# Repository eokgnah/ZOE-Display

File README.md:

# ZOE CAN ESP32

Bei diesem Projekt handelt es sich um eine Display-Platine zum Auslesen von Fahrzeugdaten (z.B. State of Health, Ladeleistung, Reifendruck) für die Renault ZOE Phase 1 (Q210, R210, R240, Q90, R90, R110, nur bis 2019).

Das Display wird mittels einer 3D-druckbaren Halterung in die Ablage unterhalb des R-Link eingelegt und über den direkt darunterliegenden OBD-Port an den CAN-Bus des Fahrzeugs angeschlossen. Es verwendet einen ESP32-Mikrocontroller mit WLAN-Funktionalität und kann per Webbrowser konfiguriert werden. 

Weitere Informationen und Bilder gibt es im GoingElectric-Forum unter https://www.goingelectric.de/forum/viewtopic.php?t=37914

Platine V5 wird über den USB-Port des R-Link mit Strom versorgt. 

Bei den Platinen V7 und V8 erfolgt die Stromversorgung über den OBD-Port. Hierbei schaltet sich die Platine beim Aufschließen des Fahrzeugs oder Starten eines Ladevorgangs automatisch ein (sobald der CAN-Bus aktiv ist). Nach Abschließen des Fahrzeugs bzw. Beendigung des Ladevorgangs kann sich das Display nach einer konfigurierbaren Zeitdauer auch selbst wieder ausschalten.
Optional kann eine USB-Buchse integriert werden, über welche beispielsweise Mobilgeräte aufgeladen werden können.

Für die Platine V8 existiert eine ausführliche Lötanleitung unter https://github.com/eokgnah/ZOE-Display/blob/master/Platine%20V8/README.md.
Der Aufbau sollte damit auch für Unerfahrene kein allzu großes Problem darstellen.

<pre>
!!!!!!!!!!!!!!!!!!!!!!!!!!!!!!!!!!!!!!!!!!!!!!!!!!!!!!!!!!!!!!!!!!
!!!! OHNE GEWÄHR, ALLES AUF EIGENE GEFAHR, NUR ZU TESTZWECKEN !!!!
!!!!!!!!!!!!!!!!!!!!!!!!!!!!!!!!!!!!!!!!!!!!!!!!!!!!!!!!!!!!!!!!!!
</pre>

## Verwendete Bauteile

- ESP32-Development-Board 38-Pin-Variante (z.B. https://www.berrybase.de/esp32-nodemcu-development-board oder https://www.ebay.de/itm/122795614934 oder https://www.amazon.de/gp/product/B071P98VTG)
- 2,8 Zoll 240 x 320 SPI TFT Panel resistiver Touchscreen (mit Display-Treiber ILI9341, z.B. https://www.ebay.de/itm/284811606229 oder https://www.amazon.de/dp/product/B082QVKT7M oder https://de.aliexpress.com/item/1005002233178546.html [Variante TL9341])
- alternativ mit kapazitivem Touchscreen (Adafruit 1947 mit Display-Treiber ILI9341, z.B. https://www.exp-tech.de/displays/tft/5430/adafruit-2.8-tft-touch-shield-for-arduino-w/capacitive-touch oder https://www.amazon.de/gp/product/B00R3R65C0/ oder https://www.mouser.de/ProductDetail/Adafruit/1947?qs=GURawfaeGuArmJSJoJoDJA%3D%3D)
- SD-Karte (bei resistivem Touchscreen) bzw. microSD-Karte (bei kapazitivem Touchscreen)
- optional GPS-Modul NEO-6M (z.B. https://www.berrybase.de/u-blox-neo-6m-gps-ttl-empfaenger-inkl.-antenne oder https://www.amazon.de/gp/product/B088LR3488 oder https://www.ebay.de/itm/265640015319)
- Kleinteile (siehe Ordner zur jeweiligen Platinen-Version)

## Verbindungen mit resistivem Touchscreen
<pre>
ESP32 Dev Board Pinout

Wohin           Bezeich.       ESP32 Pins       Bezeich.    Wohin

                            3V3         GND
                            EN          G23     MOSI        Display,Touch,SD
                ST          G36         G22
                            G39         G1      (TX)
                            G34         G3      (RX)
                (CAN2 RX)   G35         G21     CS          Touch
                (CAN2 TX)   G32         GND
                HR          G33         G19     MISO        Display,Touch,SD
                            G25         G18     SCLK        Display,Touch,SD
GPS-Modul       GPS TX      G26         G5 
GPS-Modul       GPS RX      G27         G17     CAN TX      OBD-Anschluss
BUZZER+                     G14         G16     CAN RX      OBD-Anschluss
                POWER OFF   G12         G4      RST         Display
                            GND         G0      (BOOT)
SD              CS          G13         G2      DC          Display
                (Flash)     G9          G15     CS          Display
                (Flash)     G10         G8      (Flash)
                (Flash)     G11         G7      (Flash)
                            5V          G6      (Flash)
</pre>                    
RX und TX gibt den Pin an, mit dem es verbunden werden muss. GPS TX muss also auf den Pin
TX am GPS Modul! 

CAN2 ist derzeit experimentell. 

ST = Screen Turn, ST=1 (verbinden mit 3V3) -> Bildschirm um 180 Grad gedreht

HR = Helligkeitsregelung, kann einen Transistor ansteuern, über den die LED-Hintergrundbeleuchtung des Displays gedimmt werden kann.

POWER OFF = Ausschalt-Pin für die Stromversorgung über den OBD-Port

## Verbindungen mit kapazitivem Touchscreen
<pre>
ESP32 Dev Board Pinout

Wohin           Bezeich.       ESP32 Pins       Bezeich.    Wohin

                            3V3         GND
                            EN          G23     SPI MOSI    Display
                ST          G36         G22     I²C SCL     Display
                            G39         G1      (TX)
                            G34         G3      (RX)
                (CAN2 RX)   G35         G21 
                (CAN2 TX)   G32         GND
Display         HR          G33         G19     SPI MISO    Display
Display         I²C SDA     G25         G18     SPI SCLK    Display
GPS-Modul       GPS TX      G26         G5
GPS-Modul       GPS RX      G27         G17     CAN TX      OBD-Anschluss
BUZZER+                     G14         G16     CAN RX      OBD-Anschluss
                POWER OFF   G12         G4      RST         Display
                            GND         G0      (BOOT)
Display         CARDCS      G13         G2      DC          Display
                (Flash)     G9          G15     CS          Display
                (Flash)     G10         G8      (Flash)
                (Flash)     G11         G7      (Flash)
                            5V          G6      (Flash)
</pre>                    
RX und TX gibt den Pin an, mit dem es verbunden werden muss. GPS TX muss also auf den Pin
TX am GPS Modul! 

CAN2 ist derzeit experimentell. 

ST = Screen Turn, ST=1 (verbinden mit 3V3) -> Bildschirm um 180 Grad gedreht

HR = Helligkeitsregelung, an Pin GPIO33 liegt ein PWM Signal an, welches über Pin D5 am Display
(neben CARDCS) die Regelung der Displayhelligkeit erlaubt. Achtung: Die Lötbrücke #5 auf der 
Displayplatine muss hierfür gesetzt werden.

POWER OFF = Ausschalt-Pin für die Stromversorgung über den OBD-Port
                    
## Allgemein
-  Beim Betrieb des resistiven Displays mit 3,3 V sollte der Jumper J1 am Display gesetzt (verbunden) werden (Ausschalten
des Spannungsreglers des Displays, sonst sinken die 3,3 V auf irgendwas unter 3 V). Der Touch IRQ Pin bleibt leer.
- Das Display mit kapazitivem Touchscreen erhält 5 V Versorgungsspannung. Falls das verwendete Display keine IOREF-Lötbrücke besitzt bzw. diese auf 5 V gesetzt wurde, muss eine geeignete Maßnahme vorgesehen werden, um die Spannungspegel am I²C-Bus auf max. 3,3 V zu begrenzen (das Display zieht die Leitungen nämlich mit 10-kΩ-Pull-Up-Widerständen gegen 5 V).

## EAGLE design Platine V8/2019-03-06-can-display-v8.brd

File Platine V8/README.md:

# Platine V8 — Lötanleitung

von Michi (Kontakt: kepppfeff@outlook.de oder im GoingElectric-Forum: kepppfeff-ZOE)

<pre>
!!!!!!!!!!!!!!!!!!!!!!!!!!!!!!!!!!!!!!!!!!!!!!!!!!!!!!!!!!!!!!!!!!
!!!! OHNE GEWÄHR, ALLES AUF EIGENE GEFAHR, NUR ZU TESTZWECKEN !!!!
!!!!!!!!!!!!!!!!!!!!!!!!!!!!!!!!!!!!!!!!!!!!!!!!!!!!!!!!!!!!!!!!!!
</pre>

## Benötigte Bauteile

Zusätzlich zu den unter https://github.com/eokgnah/ZOE-Display/blob/master/README.md aufgelisteten Hauptkomponenten und dem 3D-Druck werden die folgenden Bauteile benötigt. 

#### Module & Halbleiter
- U2: Spannungsregler OKI-78SR-5/1.5-W36-C oder vergleichbar (Ausgang 5 V, 1500...2000 mA)
  - Bezugsquellen: z.B. https://www.tme.eu/de/details/amsr2-7805jz/dc-dc-wandler/aimtec/ oder https://www.reichelt.de/dc-dc-wandler-oki-78sr-8-w-5-v-1500-ma-sil-single-oki515w36c-p140735.html oder https://www.voelkner.de/products/1038830/
  - Falls keine USB-Buchse an die Platine angeschlossen werden soll, kann stattdessen auch ein schwächerer (günstigerer) Spannungsregler verwendet werden, z.B. LC78_05-0.5 oder vergleichbar (Ausgang 5 V, 500 mA)
- U3: Spannungsregler LC78_03-0.5 oder LMO78_03-0.5 oder vergleichbar (Ausgang 3,3 V, 500 mA)
  - Bezugsquellen: z.B. https://www.tme.eu/de/details/amsro-783.3-nz/dc-dc-wandler/aimtec/ oder https://www.reichelt.de/dc-dc-wandler-1-65-w-3-3-v-500-ma-sil-lmo78-03-0-5-p242833.html oder https://www.voelkner.de/products/1038822/
  - Stattdessen kann auch der interne Spannungsregler des ESP32-Boards verwendet werden, dieser ist jedoch nicht so effizient und sorgt für zusätzliche Aufheizung des Mikrocontrollers, was evtl. dessen Lebensdauer verringert.
- Q1: P-Kanal-MOSFET IRFU9024N
- IC4: CAN-Transceiver MCP2562 (DIP8)
- D3, D4: Schottky-Dioden 1N5817
- T1: NPN-Transistor BC547C (nur bei Verwendung des kapazitiven Displays)
- T4: PNP-Transistor BC327-25
- T5, T6: NPN-Transistoren BC547C

#### Passive Bauelemente
- R1: Widerstand 100 kΩ ± 50 % (nur bei Verwendung des kapazitiven Displays)
- R3: Widerstand 1,5 kΩ ± 5 % (nur bei Verwendung des resistiven Displays mit eingebautem Transistor, siehe weiter unten) bzw. Widerstand 5,1 Ω ± 5 % (nur bei Verwendung des resistiven Displays ohne eingebauten Transistor, siehe weiter unten)
- R4: Widerstand 15 kΩ ± 5 % (nur bei Verwendung des kapazitiven Displays der alten Version, siehe weiter unten)
- R5: Widerstand 120 Ω ± 10 %
- R6: Widerstand 15 kΩ ± 5 %
- R7: Widerstand 15 kΩ ± 5 % (nur bei Verwendung des kapazitiven Displays der alten Version, siehe weiter unten)
- R8: Widerstand 100 kΩ ± 5 %
- R9: Widerstand 470 kΩ ± 10 %
- R10, R11: Widerstände 1,2 MΩ ± 5 %
- R12: Widerstand 470 kΩ ± 5 %
- R13: Widerstand 47 kΩ ± 5 %
- C1: Elektrolyt-Kondensator 10 μF, min. 10 V
- C2, C3, C4: Keramik-Kondensatoren 100 nF
- C5: Elektrolyt-Kondensator 10 μF, min. 25 V
- C6: Elektrolyt-Kondensator 22 μF, min. 6,3 V

#### Steckverbinder & Elektromechanik
- OBD-Stecker (z.B. https://kds-online.de/de/obd-minitools-modular-system-stecker-e.html oder https://www.tme.eu/de/details/a-obd-e2/gehause-sonstiges-zubehor/minitools/sep-a-obd-e2/)
- Piezo-Summer, mit Kabeln oder für Printmontage (RM 7,6 mm)
- IC-Sockel DIP8 (für MCP2562)
- USB-Buchse (optional)
- Schraubklemmblock 3-polig (RM 5 mm) für Stromversorgung (12 V Eingang, 5 V Ausgang)
- Schraubklemmblock 2-polig (RM 5 mm) für CAN-Bus
- Kabel zum Anschluss von OBD-Stecker und ggf. USB-Buchse
- Stiftleisten (für GPS-Modul, resistives Display und ggf. als Abstandshalter)

## Grundlegendes Vorgehen

Wer bereits Platinen bestückt hat, kann diesen Abschnitt gerne überspringen ;-)

Zum Zusammenbau des ZOE-Displays benötigt ihr Folgendes:
- Lötkolben und Lötzinn, Lötspitzen-Reinigungstool (feuchter Schwamm, Spiralwolle etc.)
- Seitenschneider bzw. Vornschneider
- Spitzzange
- Abisolierzange
- Schlitz-Schraubendreher
- Heißklebepistole und -sticks, alternativ 2-Komponenten-Kleber oder ähnliches
- Eventuell (falls ihr etwas falsch verlötet habt): Entlötsaugpumpe, Entlötlitze etc.

Bei dieser Platine werden alle Bauteile in Durchsteckmontage (Printmontage) bestückt. Die grundlegende Vorgehensweise, um ein Bauteil einzulöten, ist Folgende:

1. Anschlussdrähte des Bauteils zurechtbiegen (falls nötig).
2. Bauteil von der Seite der Platine, auf der der Bestückungsdruck für das Bauteil angebracht ist, durch die entsprechenden Kontaktlöcher stecken.
3. Platine umdrehen und die herausragenden Drähte (bzw. Metallstifte) nacheinander mit den Leiterbahnen verlöten. Zum Löten sollte man in der Regel zuerst den Lötkolben an die beiden zu verlötenden Metallteile halten (hier Draht und Leiterplattenkontakt), sodass die Lötspitze *beide* Teile erhitzt. Direkt anschließend gibt man das Lötzinn hinzu, welches sich nun kegelförmig (nicht kugelförmig :D) um den Draht verteilen sollte. 
4. Alle überstehenden Drähte abschneiden, und zwar möglichst direkt an der Lötstelle.

Hierbei kann man entweder alle Bauteile einzeln nacheinander durchstecken und verlöten oder auch mehrere auf einmal. Damit die Bauteile während des Lötens nicht nach unten aus der Platine herausrutschen können, macht es Sinn, mit den flachsten Bauteilen anzufangen und sich nach und nach zu den höchsten Bauteilen vorzuarbeiten. Im Idealfall liegt die Platine dann immer auf dem Bauteil auf, welches als Nächstes angelötet werden soll. 

Wenn ihr noch nie Bauteile auf eine Platine gelötet habt, ist es sicherlich hilfreich, vorher mal ein entsprechendes Tutorial-Video z.B. auf Youtube anzuschauen.

## Hinweise zum resistiven Touchscreen

Bei Verwendung des Displays mit resistivem Touchscreen werden die Widerstände R1, R4 und R7 sowie der Transistor T1 nicht benötigt.

Falls ihr das Display mit resistivem Touchscreen verwendet, solltet ihr zunächst prüfen, ob dieses einen eingebauten Transistor für die LED-Hintergrundbeleuchtung eingebaut hat oder nicht. Nur wenn ein Transistor eingebaut ist, könnt ihr die Helligkeit des Displays steuern.
Von der Versionsbezeichnung des Displays hängt dies scheinbar nicht ab; ich habe schon Bilder von V1.1 und V1.2 jeweils sowohl mit und ohne Transistor gesehen! Ihr müsst also tatsächlich den Transistor auf der Display-Platine suchen. Es handelt sich um ein kleines schwarzes Bauteil mit drei Pins, welches auf der Platine mit **Q1** beschriftet sein muss (es gibt eventuell ein gleich aussehendes Bauteil, welches anders beschriftet ist, das ist aber kein Transistor, sondern ein Spannungsregler). 
- Falls euer Display *zwei* kleine schwarze Bauteile mit je drei Pins hat, von denen eines mit U1 und eines mit Q1 beschriftet ist, dann habt ihr ein Display *mit* eingebautem Transistor. **In diesem Fall muss für R3 ein 1,5-kΩ-Widerstand eingesetzt werden. Außerdem sollte die Lötbrücke SJ5 gesetzt werden, damit die Display-Helligkeit vom ESP32 gesteuert werden kann.**
- Falls euer Display nur *ein* kleines schwarzes Bauteil mit drei Pins hat, dann hat das Display *keinen* Transistor eingebaut. **In diesem Fall muss für R3 ein 5,1-Ω-Widerstand eingesetzt werden (anders als auf dem Bestückungsdruck angegeben!). Die Lötbrücke SJ5 muss offen bleiben, da sonst der ESP32 Schaden nehmen kann!**

In der Regel müsst ihr auf euer Display noch eine 4-polige Stiftleiste für die Anschlüsse der SD-Karte einlöten. Hier darauf achten, dass ihr diese möglichst gerade montiert, damit das Display später perfekt auf die Platine passt. Am Besten gelingt dies, wenn ihr das Display zum Anlöten der 4-polige Stiftleiste lose in die entsprechenden Kontaktlöcher der (noch unbestückten) Platine legt.

Das resistive Display besitzt zudem eine Lötbrücke (J1), die ggf. gesetzt werden muss. Hierzu bitte den Abschnitt „Hinweise zu den Lötbrücken zur Auswahl der Stromversorgung“ beachten.

## Hinweise zum kapazitiven Touchscreen

Bei Verwendung des Displays mit kapazitivem Touchscreen wird der Widerstand R3 nicht benötigt.

Falls ihr das Display mit kapazitivem Touchscreen verwendet, solltet ihr zunächst prüfen, ob ihr die alte oder die neue Version des Displays besitzt. Kleine Anmerkung am Rande: Auf den beiden folgenden Fotos wurde jeweils rechts die 6-polige ISP-Buchse abgelötet, dies ist jedoch bei der Platine V8 nicht erforderlich!

### Alte Version

Hier müsst ihr lediglich die Lötbrücke „backlight #5“ setzen, wie im Foto zu sehen, damit die LED-Hintergrundbeleuchtung gedimmt werden kann. Die Lötbrücken „13“, „12“ und „11“ sind bei dieser Version bereits standardmäßig (über feine Leiterbahnen) gesetzt.

**Bei der Bestückung der Platine sind die beiden 15-kΩ-Widerstände R4 und R7 zwingend erforderlich, da ohne diese der ESP32 eine zu hohe Spannung vom Display abbekommt.**

### Neue Version

Wie man sieht, gibt es hier die zusätzliche Lötbrücke IOREF. Diese müsst ihr (anders als im Foto!) auf 3,3 V setzen, also das mittlere und das linke (mit „3V“ beschriftete) Pad mit einem Tropfen Lötzinn verbinden. 

**Bei der Bestückung der Platine sollten dann die beiden 15-kΩ-Widerstände R4 und R7 weggelassen werden.**

Außerdem müsst ihr die Lötbrücken „backlight #5“, „13“, „12“ und „11“ setzen (wie im Foto zu sehen).

## Hinweise zu den Lötbrücken zur Auswahl der Stromversorgung

Der 3,3-V-Spannungsregler **U3** (LC78_03-0.5 oder ähnlich) ist nicht unbedingt erforderlich, da alternativ auch der interne (lineare) Spannungsregler des ESP32 verwendet werden kann. Zur Auswahl zwischen diesen beiden Varianten dienen die Lötbrücken SJ2, SJ3 und SJ4.

### Falls die Platine mit Spannungsregler U3 bestückt wird, ...

... werden ESP32, GPS-Modul und resistives Display vom Spannungsregler U3 mit 3,3 V versorgt. 

**Hierzu muss die Lötbrücke SJ4 gesetzt werden. Bei Verwendung des resistiven Displays muss zusätzlich dessen Lötbrücke J1 gesetzt werden.**

Wenn die Platine nur über den USB-Port des ESP32 betrieben wird (z.B. zum Flashen), ist das kapazitive Display bei dieser Schaltungsvariante nicht in Betrieb! Wer dies ändern möchte, kann zusätzlich die Lötbrücke SJ2 setzen, allerdings wird dadurch bei Versorgung über den OBD-Port die Spannungswandlung ineffizienter, da der interne Spannungsregler des ESP32 ständig „mitläuft“.

### Falls der Spannungsregler U3 weggelassen wird, ...

... werden ESP32, GPS-Modul und resistives Display vom Spannungsregler U2 mit 5 V versorgt. Alle drei nutzen dann ihre internen linearen Spannungsregler, um die Spannungsdifferenz zu verbraten. 

**Hierzu müssen die Lötbrücken SJ2 und SJ3 gesetzt werden. Bei Verwendung des resistiven Displays muss dessen Lötbrücke J1 offen bleiben.**

## Platine löten
#### Schritt 1: Lötbrücken setzen

Als erstes solltet ihr alle benötigten Lötbrücken setzen. 

- SJ1 bestimmt über die Ausrichtung des Bildschirms. Bei Verwendung des 3D-gedruckten ZOE-Einlegers sollte diese Lötbrücke für das resistive Display normalerweise auf die Seite mit dem „S“ und für das kapazitive Display auf die Seite mit der „1“ gesetzt werden. An diese Lötbrücke kommt man auch später noch ganz gut dran, sodass es kein Problem ist, wenn sie falsch gesetzt wurde.
- Wie ihr SJ2, SJ3 und SJ4 setzen müsst, findet ihr unter „Hinweise zu den Lötbrücken zur Auswahl der Stromversorgung“.
- SJ5 sollte nur bei Verwendung eines resistiven Displays mit eingebautem Transistor gesetzt werden.

#### Schritt 2: Widerstände und Dioden

Als nächstes kommen die flachen Bauteile dran. Bei Widerständen ist die Polarität egal, bei den Dioden ist der Strich, welcher den Minuspol kennzeichnet, auf dem Bestückungsdruck eingezeichnet. 

#### Schritt 3: IC-Sockel

Damit der CAN-Transceiver-IC (IC4) nicht durch die Hitze Schaden nimmt, wird er nicht auf die Platine gelötet, sondern nur ein passender Sockel, in den der IC später eingesteckt wird. Die Einbaurichtung des ICs kann über eine einseitige Einkerbung kontrolliert werden, welche auf dem Bestückungsdruck eingezeichnet ist.

#### Schritt 4: Keramik-Kondensatoren

Nun sind C2, C3 und C4 an der Reihe. Es können Keramik-Kondensatoren mit 2,5 mm oder 5 mm Rastermaß verwendet werden. Die Polarität ist egal. 

#### Schritt 5: Piezo-Summer

Falls ein Piezo-Summer für Printmontage verbaut wird, sollte dieser je nach Abmessungen jetzt oder etwas später eingelötet werden. Bei einigen Piezo-Summern muss die Polarität beachtet werden (z.B. wenn die Beinchen verschieden lang sind, das längere ist dann Plus), bei anderen nicht.

#### Schritt 6: Stiftleiste für GPS-Modul

Als Nächstes wird eine Stiftleiste eingelötet, auf die später das GPS-Modul montiert werden kann. Das GPS-Modul selbst sollte jetzt noch nicht mit angelötet werden, da es die Anschlüsse für das kapazitive Display teilweise verdecken würde. Je nach GPS-Modul wird eine Stiftleiste mit 4 oder 5 Pins benötigt. Es empfiehlt sich, die Metallstifte etwas zu kürzen, damit sie später nicht so weit herausstehen.

Inzwischen sollte die Platine ungefähr so aussehen:

#### Schritt 7: Transistoren

Jetzt sind die bipolaren Transistoren T1, T4, T5, T6 und der MOSFET Q1 an der Reihe. Bei den bipolaren Transistoren muss jeweils der mittlere Pin vorsichtig etwas zurechtgebogen werden. Die Einbaurichtung dürfte selbsterklärend sein. Der MOSFET muss so herum eingebaut werden, dass die Beschriftung zum Rand der Platine zeigt (und die Metallfläche entsprechend in Richtung der Kabelanschlüsse). 

#### Schritt 8: Schraubklemmblöcke

Nun werden die 3-polige Schraubklemme für die Stromversorgung und die 2-polige Schraubklemme für den CAN-Bus eingelötet.

#### Schritt 9: ESP32

Die Platine ist kompatibel zu zwei verschieden großen ESP32-Boards (mit dem selben Pinout), daher ist die eine Lochreihe doppelt vorhanden. 

Bei günstigen ESP32-Boards sind oft die Stiftleisten nicht ganz gerade eingelötet, dann müsst ihr diese noch etwas zurechtbiegen, um sie in die Kontaktlöcher der Platine zu bekommen.

Damit der ESP32 nachher in der perfekten Höhe (und gerade) montiert ist, bietet es sich an, auf die vier äußersten Pins jeweils als Abstandshalter ein Plastikteil einer Stiftleiste draufzuschieben. Hierzu aus einer vierpoligen Stiftleiste alle Metallstifte herausziehen und anschließend das Plastikteil in seine vier Einzelteile zerbrechen. Am Ende sollte es dann so aussehen (hier sind zusätzlich die Abstandshalter des resistiven Touchdisplays zu sehen, beim kapazitiven werden hingegen keine benötigt):

#### Schritt 10: 3,3-V-Spannungsregler

Der 3,3-V-Spannungsregler kommt in das mit „LC78_**03**-0.5“ beschriftete Rechteck. Einbaurichtung beachten! In der Regel sollte die Bauteilbeschriftung in Richtung des POWER-Schraubklemmblocks zeigen. Bei Unsicherheit am Besten im Datenblatt nachschauen, auf der Platine ist der Eingang mit VIN und der Ausgang mit VO beschriftet. 
Falls der Spannungsregler LMO78_03-0.5 verwendet wird (wie im gleich folgenden Foto), sollte dieser eventuell ein wenig gekippt eingebaut werden, da er sonst etwas zu weit in Richtung des Kondensators C6 übersteht, sodass dieser nicht mehr richtig passt.

#### Schritt 11: Elektrolyt-Kondensatoren

Bei den Elkos (C1, C5 und C6) muss auf die Polarität geachtet werden. Der Pluspol ist durch einen längeren Draht, der Minuspol durch einen weißen Strich auf dem Gehäuse gekennzeichnet.

#### Schritt 12: 5-V-Spannungsregler

Der 5-V-Spannungsregler gehört in das mit „LC78_**05**-0.5“ beschriftete Rechteck. Einbaurichtung beachten! Bei Unsicherheit am Besten im Datenblatt nachschauen, auf der Platine ist der Eingang mit VIN und der Ausgang mit VO beschriftet.

Anschließend sollte die Platine ungefähr so aussehen:

#### Schritt 13: Display

Bevor ihr Display und Platine zusammenfügt, kontrolliert nochmal, ob alle Lötstellen gut aussehen und ob ihr am Display alle erforderlichen Lötbrücken gesetzt habt, denn ihr kommt anschließend nicht mehr dran! 

Beim kapazitiven Display empfehle ich, dieses erstmal in den 3D-gedruckten Einleger zu setzen (microSD-Karte einlegen und Schutzfolie abziehen!), anschließend die Platine darauf zu platzieren und erst dann, im „lose eingebauten Zustand“, beides zu verlöten. 

Beim resistiven Display ist dieses Vorgehen nicht erforderlich, hier bietet es sich stattdessen an, wieder vier Plastikteile einer Stiftleiste als Abstandshalter zu nutzen. Achtet darauf, dass der SD-Karten-Halter nicht mit von der Platine abstehenden Drähten in Berührung kommt. Zur Sicherheit bietet es sich an, den SD-Karten-Halter mit Kaptonband, Tesafilm oder ähnlichem zu überkleben. 

#### Schritt 14: GPS-Modul

Als Nächstes wird das GPS-Modul auf die zuvor eingelötete Stiftleiste gelötet.

#### Schritt 15: IC einsetzen

Zu guter Letzt wird der CAN-Transceiver-IC in den zuvor eingelöteten Sockel gesteckt. Ausrichtung beachten! Bei „fabrikfrischen“ ICs müssen vorher meist noch die Beinchen etwas nach innen gebogen werden. 

## Verkabelung

Die Drähte zur USB-Buchse, zum OBD-Stecker und zum Piezo-Summer (falls einer mit Kabeln verwendet wird) können auf drei verschiedene Arten an der Platine angeschlossen werden: Durch Anschrauben in angelötete Schraubklemmblöcke, über die SMD-Lötpads oder durch direktes Einlöten der Kabel in die Löcher für die Schraubklemmblöcke. 

Die Beschriftung der Anschlüsse befindet sich jeweils an den SMD-Lötpads, die direkt an die zugehörigen Schraubklemmen angrenzen.

#### USB-Buchse

Um die USB-Buchse in den 3D-gedruckten Einleger zu bekommen, müssen zunächst die beiden Montagepins des Buchsengehäuses etwas gekürzt werden. Anschließend die vier Anschlusspins (Masse, D+, D- und +5 V) nach hinten umbiegen und darauf achten, dass sie nicht mit dem Buchsengehäuse in Berührung kommen. 

An Masse (GND) und +5 V lötet ihr Drähte an, die dann an der Platine angeschlossen werden können. Achtet darauf, dass durch das Lötzinn keine Verbindung mit dem Buchsengehäuse hergestellt wird.

Die beiden Datenleitungen (die mittleren Pins) können im einfachsten Fall kurzgeschlossen werden, dies entspricht der EU-standardisierten Signalisierung eines USB-Ladegeräts. Hierzu einfach die beiden Drähte etwas zur Mitte biegen und mit einem Tropfen Lötzinn verbinden (wieder darf keine Verbindung zum Buchsengehäuse entstehen). Manche USB-Geräte akzeptieren diese Signalisierung allerdings nicht und laden nur langsam. Um die USB-Buchse für solche Geräte kompatibel zu machen, müsst ihr eventuell statt der Kurzschlussmethode bestimmte Spannungen mittels Widerständen an die Datenleitungen anlegen. Mehr Infos dazu findet ihr z.B. hier: http://dh2mic.darc.de/files/usb-adapter-v12.pdf

Zum Schluss noch alles mit Heißkleber, 2-Komponentenkleber o.ä. versiegeln, damit kein Kurzschluss entstehen kann und die USB-Buchse nicht herausrutscht.

#### OBD-Stecker

Die Belegungen einer OBD2-Schnittstelle findet ihr hier: https://commons.wikimedia.org/wiki/File:OBD2-Buchse-Stecker-Belegung.jpg

Vier Pins werden benötigt: Fahrzeugmasse (GND) und +12 V zur Stromversorgung sowie CAN High und CAN Low zur Datenübertragung. 

Achtung: Den Lötkolben nicht zu lange an die Metallstifte des OBD-Steckers halten, da sonst das Plastik drumherum aufweicht, wodurch der Metallstift sich womöglich leicht verdreht oder verschiebt. Alternativ können die Metallstifte zum Anlöten der Drähte aus dem Steckergehäuse herausgenommen und anschließend wieder eingesetzt werden. Die oben verlinkten OBD-Stecker sind nur zusammengesteckt und die Stifte werden von einer eingeklipsten Plastikkappe gehalten.

Wenn ihr den 3D-gedruckten ZOE-Einleger verwendet, müsst ihr die Kontaktstifte des OBD-Steckers zur Seite umbiegen (bzw. die unbenutzten abschneiden oder entfernen), da diese sonst zu weit herausstehen. Das sollte dann etwa so aussehen. 

Anschließend sollten die Lötstellen unbedingt noch z.B. mit Heißkleber oder Schrumpfschläuchen umhüllt werden, damit kein Kurzschluss entstehen kann und die Drähte nicht mit der Zeit (z.B. durch Vibrationen) abbrechen können.

#### Schraubklemmblöcke

Um die Drähte gut in den Schraubklemmblöcken befestigen zu können, sollten die Enden jeweils verdrillt und mit dem Lötkolben verzinnt werden. Wer über das entsprechende Equipment verfügt, kann (und soll) natürlich stattdessen Aderendhülsen verwenden. 

Wer eine USB-Buchse verwendet, muss zwei GND-Drähte in eine Schraubklemme zwängen. Hierzu sollten diese beiden Drähte zusammen verzinnt bzw. zusammen in eine Aderendhülse gecrimpt werden.

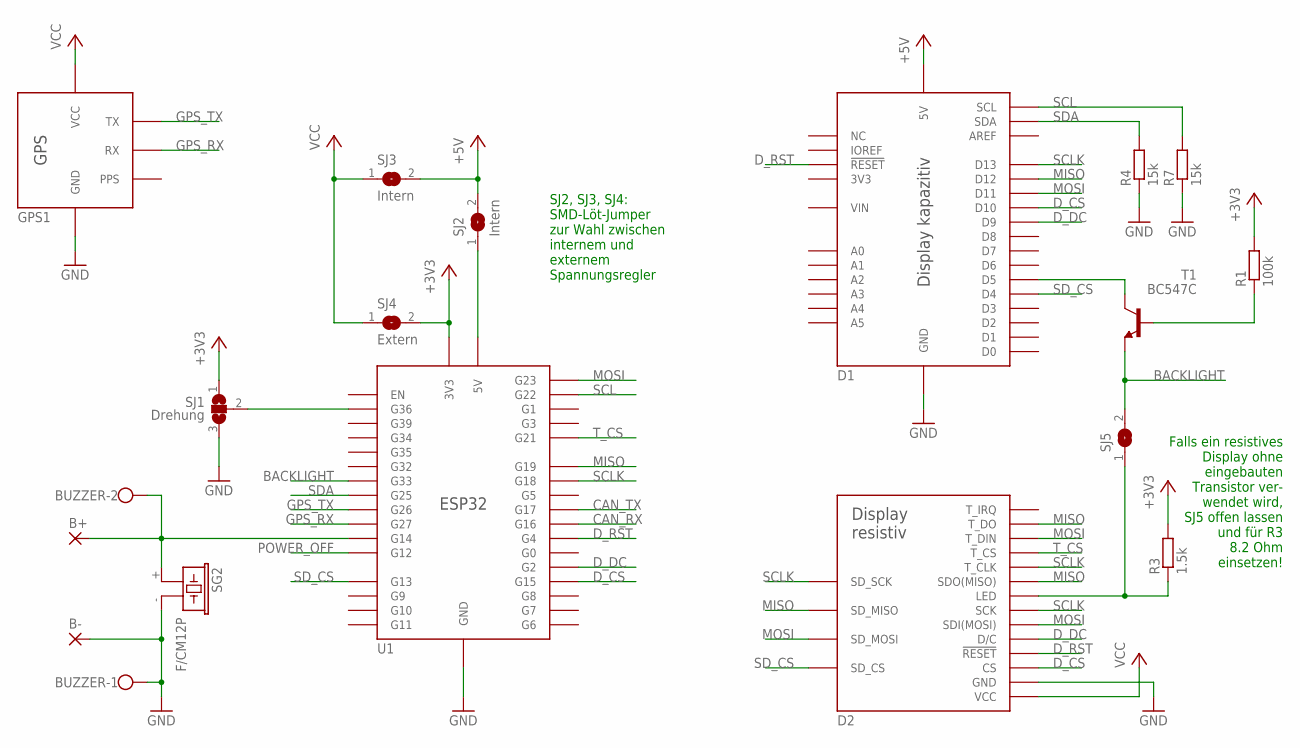
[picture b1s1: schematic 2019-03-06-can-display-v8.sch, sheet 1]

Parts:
B+: WIREPADSMD5-2,5; 5-2,5
B-: WIREPADSMD5-2,5; 5-2,5
BUZZER: W237-102
D1: TFT-KAPAZITIV
D2: TFT-RESISTIV
GPS1: GPS
R1: 100k; VMTA55
R3: 1.5k; VMTA55
R4, R7: 15k; VMTA55
SG2: F/CM12P
SJ1: Drehung; SJ_2
SJ2, SJ3: Intern; SJ
SJ4: Extern; SJ
SJ5: const.; SJ
T1: BC547C; TO92
U1: ESP32

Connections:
+3V3: R1.2, R3.2, SJ1.1, SJ4.2, U1.3V3, U1.3V3S (3V3); also elsewhere on the board
+5V: D1.5V, SJ2.2, SJ3.2; also elsewhere on the board
BACKLIGHT: SJ5.2, T1.1 (E), U1.G33, U1.G33S (G33)
CAN_RX: U1.G16; also elsewhere on the board
CAN_TX: U1.G17; also elsewhere on the board
D_CS: D1.D10, D2.LCD_CS (CS), U1.G15
D_DC: D1.D9, D2.LCD_DC (D/C), U1.G2
D_RST: D1.RESET (!RESET!), D2.LCD_RESET (!RESET!), U1.G4
GND: B-.1, BUZZER.1, D1.GND@1 (GND), D1.GND@2 (GND), D1.GND@3 (GND), D2.GND, GPS1.GND1 (GND), GPS1.GND2 (GND), R4.1, R7.1, SG2.- (2), SJ1.3, U1.GND@1 (GND), U1.GND@2 (GND), U1.GND@3 (GND), U1.GND@4 (GND); also elsewhere on the board
GPS_RX: GPS1.RX1 (RX), GPS1.RX2 (RX), U1.G27, U1.G27S (G27)
GPS_TX: GPS1.TX1 (TX), GPS1.TX2 (TX), U1.G26, U1.G26S (G26)
MISO: D1.D12, D2.LCD_MISO (SDO(MISO)), D2.SD_MISO, D2.T_DO, U1.G19
MOSI: D1.D11, D2.LCD_MOSI (SDI(MOSI)), D2.SD_MOSI, D2.T_DIN, U1.G23
unnamed: SJ1.2, U1.G36, U1.G36S (G36)
unnamed: D1.D5, T1.3 (C)
unnamed: D2.LED, R3.1, SJ5.1
unnamed: R1.1, T1.2 (B)
unnamed: B+.1, BUZZER.2, SG2.+ (1), U1.G14, U1.G14S (G14)
unnamed: SJ2.1, U1.5V, U1.5VS (5V)
POWER_OFF: U1.G12, U1.G12S (G12); also elsewhere on the board
SCL: D1.KAP_SCL (SCL), R7.2, U1.G22
SCLK: D1.D13, D2.LCD_SCK (SCK), D2.SD_SCK, D2.T_CLK, U1.G18
SDA: D1.KAP_SDA (SDA), R4.2, U1.G25, U1.G25S (G25)
SD_CS: D1.D4, D2.SD_CS, U1.G13, U1.G13S (G13)
T_CS: D2.T_CS, U1.G21
VCC: D2.VCC, GPS1.VCC1 (VCC), GPS1.VCC2 (VCC), SJ3.1, SJ4.1; also elsewhere on the board

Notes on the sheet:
SJ2, SJ3, SJ4: SMD-Löt-Jumper zur Wahl zwischen internem und externem Spannungsregler
Falls ein resistives Display ohne eingebauten Transistor ver- wendet wird, SJ5 offen lassen und für R3 8.2 Ohm einsetzen!

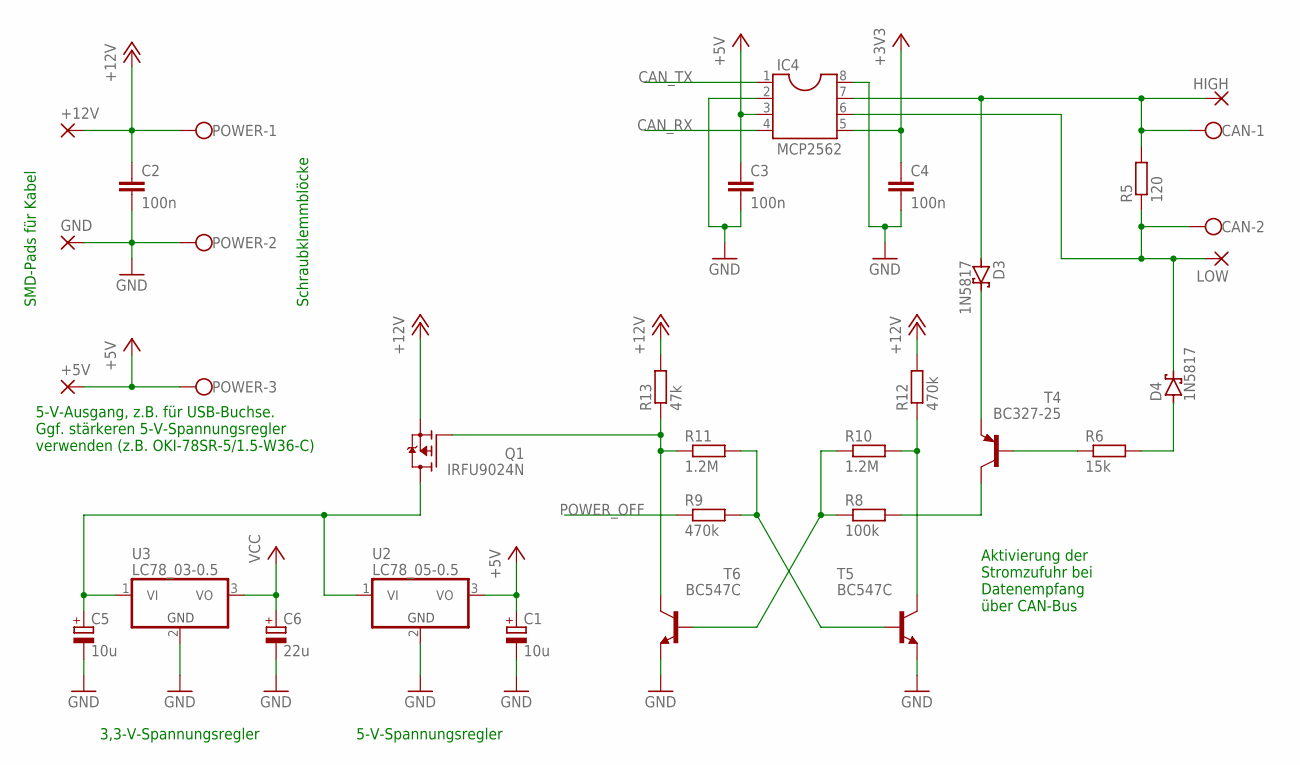
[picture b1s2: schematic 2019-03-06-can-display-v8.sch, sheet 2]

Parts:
+5V, +12V: WIREPADSMD5-2,5; 5-2,5
C1, C5: 10u; E1,8-4
C2, C3, C4: 100n; C025_050-024X070
C6: 22u; E1,8-4
CAN: W237-102
D3, D4: 1N5817; DO41-7.6
GND: WIREPADSMD5-2,5; 5-2,5
HIGH: WIREPADSMD5-2,5; 5-2,5
IC4: MCP2562; DIL08
LOW: WIREPADSMD5-2,5; 5-2,5
POWER: W237-103
Q1: IRFU9024N; TO251AA-V
R5: 120; VMTA55
R6: 15k; VMTA55
R8: 100k; VMTA55
R9, R12: 470k; VMTA55
R10, R11: 1.2M; VMTA55
R13: 47k; VMTA55
T4: BC327-25; TO92
T5, T6: BC547C; TO92
U2: LC78_05-0.5; SPANNUNGSREGLER
U3: LC78_03-0.5; SPANNUNGSREGLER

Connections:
+3V3: C4.3 (1), IC4.5; also elsewhere on the board
+5V: +5V.1, C1.+, C3.3 (1), IC4.3, POWER.3, U2.3 (VO); also elsewhere on the board
+12V: +12V.1, C2.3 (1), POWER.1, Q1.3 (S), R12.2, R13.2
CAN_RX: IC4.4; also elsewhere on the board
CAN_TX: IC4.1; also elsewhere on the board
GND: C1.-, C2.1 (2), C2.2, C3.1 (2), C3.2, C4.1 (2), C4.2, C5.-, C6.-, GND.1, IC4.2, IC4.8, POWER.2, T5.1 (E), T6.1 (E), U2.2 (GND), U3.2 (GND); also elsewhere on the board
unnamed: D3.C, T4.1 (E)
unnamed: R6.1, T4.2 (B)
unnamed: D4.A, R6.2
unnamed: R8.1, R10.1, T6.2 (B)
unnamed: CAN.1, D3.A, HIGH.1, IC4.7, R5.2
unnamed: CAN.2, D4.C, IC4.6, LOW.1, R5.1
unnamed: R8.2, T4.3 (C)
unnamed: R9.2, R11.2, T5.2 (B)
unnamed: R10.2, R12.1, T5.3 (C)
unnamed: Q1.1 (G), R11.1, R13.1, T6.3 (C)
unnamed: C5.+, Q1.2 (D), U2.1 (VI), U3.1 (VI)
POWER_OFF: R9.1; also elsewhere on the board
VCC: C6.+, U3.3 (VO); also elsewhere on the board

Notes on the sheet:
3,3-V-Spannungsregler
5-V-Spannungsregler
Aktivierung der Stromzufuhr bei Datenempfang über CAN-Bus
SMD-Pads für Kabel
Schraubklemmblöcke
5-V-Ausgang, z.B. für USB-Buchse. Ggf. stärkeren 5-V-Spannungsregler verwenden (z.B. OKI-78SR-5/1.5-W36-C)

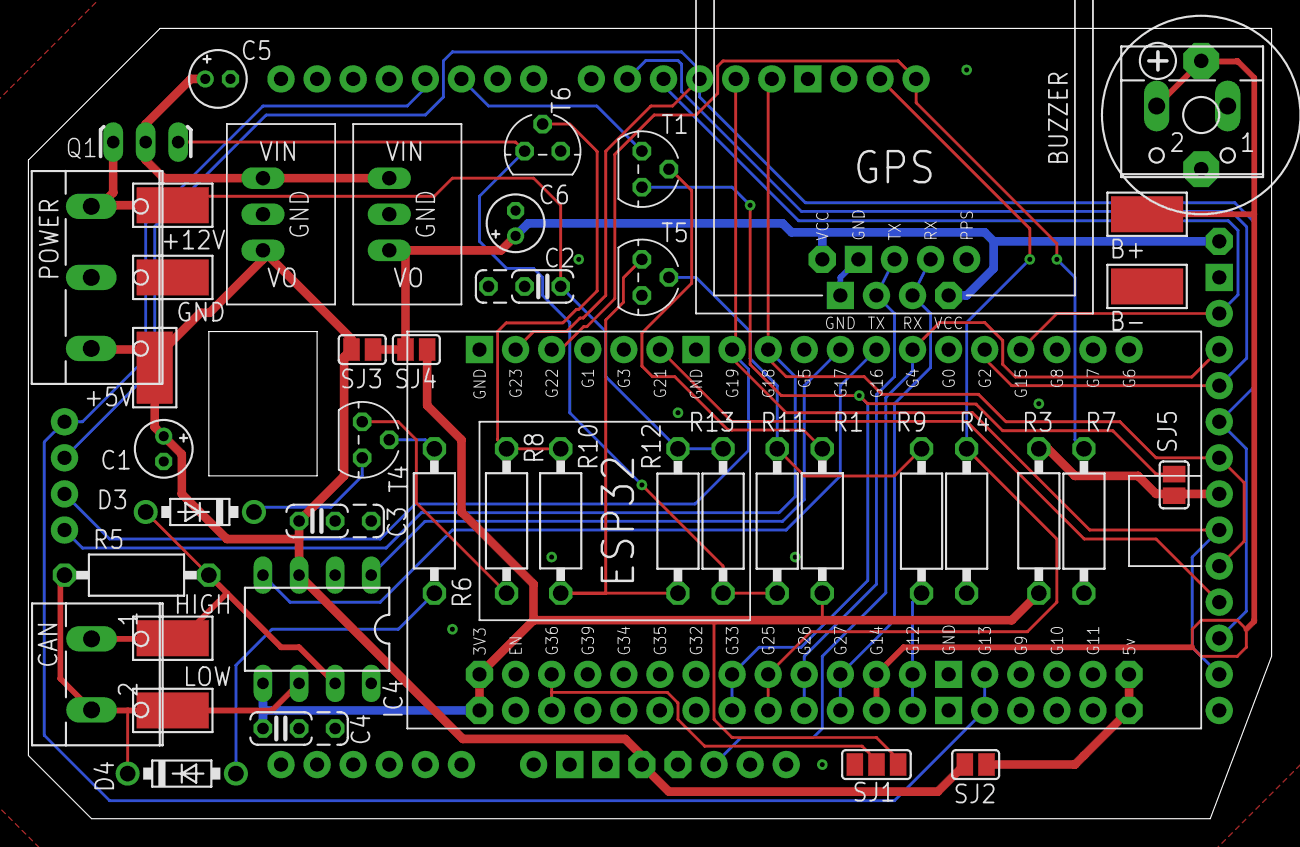
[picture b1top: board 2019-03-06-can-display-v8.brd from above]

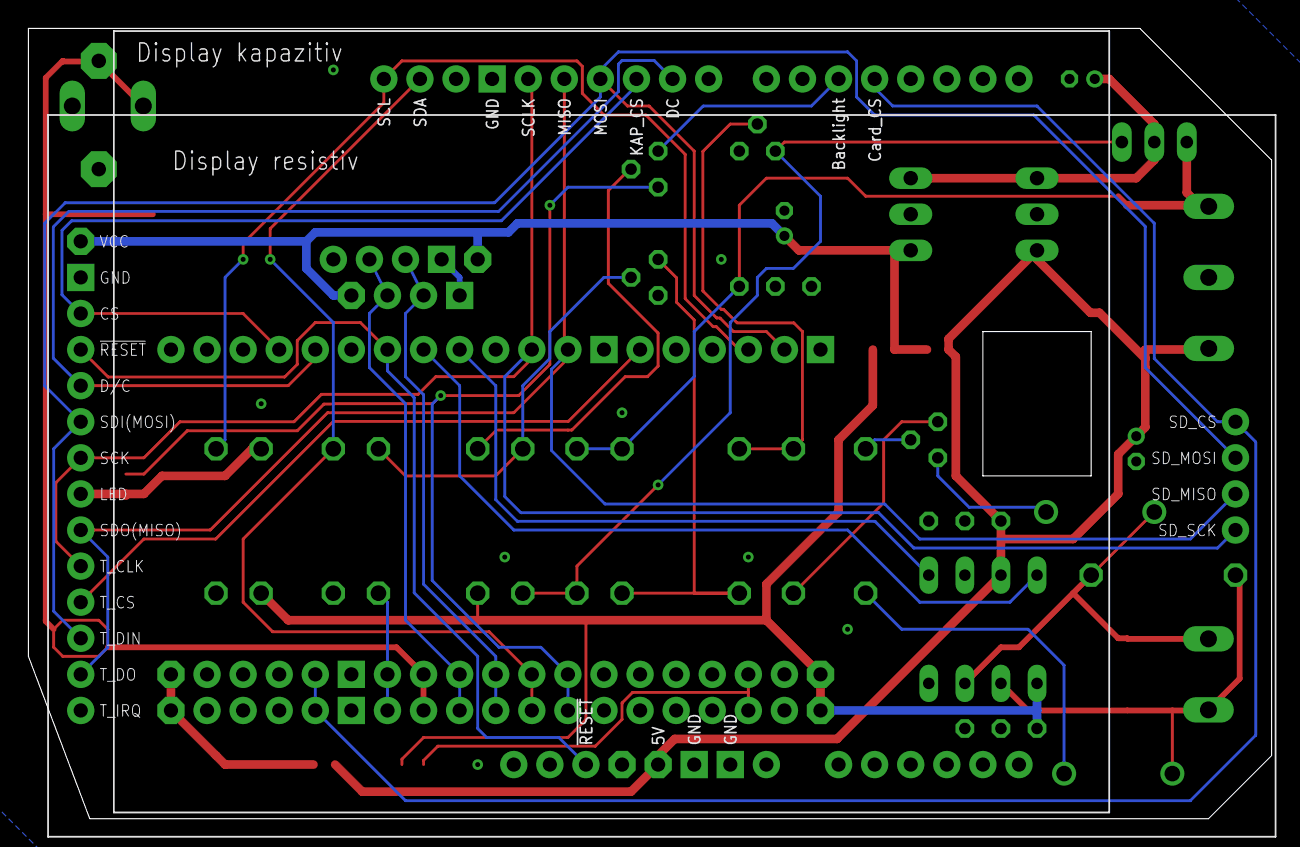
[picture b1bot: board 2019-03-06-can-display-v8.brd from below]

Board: 2 copper layers, 87.5 x 55.6 mm, 48 parts (2 on the bottom side), 38 nets.

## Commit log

2019-02-26 Create README.md
    New Folder for V7
2019-02-26 Move 00-arduino-einstellungen.PNG
2019-02-26 Move 01-esp32-vorbereiten.PNG
2019-02-26 Move 02-ZOE-flashen.PNG
2019-02-26 Move CAN-ESP32.SMART.esp32-v2.075.bin
2019-02-26 Move CAN-ESP32.ZOE.esp32-v2.072.bin
2019-02-26 Move CAN-ESP32.ZOE.esp32-v2.075.bin
2019-02-26 Move 2018-11-10-can-display-v5_2018-11-10.zip
2019-02-26 Move Can-Display-v5.png
2019-02-26 Move Zoe-Einleger-Kapa-V6.stl
2019-02-26 Move Zoe-Einleger-Resisitv-V6.stl
2019-03-03 Add values for R1 and R3
2019-03-08 Add product links
2019-03-12 Add part links
2021-06-29 Update product links
2021-06-29 Add exp-tech link for capacitive touchscreen
2025-06-12 remove outdated link
